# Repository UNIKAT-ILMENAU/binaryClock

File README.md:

# Notizen

## Idee

- QRCode mit Link auf Webseite für Flackercode Config Tool
- vllt Pads für I2C und ISP rausführen
- auf PCB, welche LED welcher Modus ist
- Comic Design? (muss zu Skyline passen)

## Hardware
- Fotodioden/transistoren
    - SFH 229 OSO
    - SFH 203
    - PT 334-6C EVL
    - SFH 309-5 OSO
    - SFH 300-3/4
- Batteriehalter: https://www.mouser.de/ProductDetail/Linx-Technologies/BAT-HLD-012-SMT?qs=Z0V%2FpEl%252BOGfZsSJil9WIXw%3D%3D
- Micro USB Port: https://www.mouser.de/ProductDetail/CUI-Devices/UJ2-MIBH-G-SMT-TR?qs=IS%252B4QmGtzzpvS1XQusp0iA%3D%3D

## Lötreihenfolge
- Quartz
- Widerstände
- LED
- Taster
- Sockel
- Kondensatoren

## Software
- https://forum.arduino.cc/t/time-libary-sommerzeit-winterzeit/221884

### Modi
Button 1: Select
Button 2: Plus
Button 3: Minus

Select rotiert durch die Zustände, Plus und Minus verändern den Wert

- TimeRunning, Zeit wird angezeigt und zählt          
- MenuYear, Jahr setzen
- MenuMonth, Monat setzen
- MenuDay, Tag setzen
- MenuHour, Stunden setzen
- MenuMinute, Minuten setzen
- MenuSecond, Sekunden setzen 

## ADC Calculation
| No. Switches    |           3 |        | Button No. | Req'd ADC | Req'd V (R1) | Req'd V (R2+) | Req'd R | Closest R | Actual V (R1) | Actual V (R2+) | Actual ADC | Diff from prev. | In Tolerance | Current (mA) |
|-----------------|------------:|--------|-----------:|----------:|-------------:|--------------:|--------:|----------:|--------------:|---------------:|-----------:|----------------:|-------------:|-------------:|
| ADC Resolution  |        1024 |        |          0 |      1024 |         0.00 |          5.00 |   47000 |     47000 |          5.00 |           0.00 |          0 |               0 |          N/A |         0.11 |
| Tolerance (%)   |           2 |        |          1 |       341 |         3.33 |          1.67 |   23500 |     24000 |          3.31 |           1.69 |        346 |             346 |          YES |         0.07 |
| Voltage         |           5 |        |          2 |       683 |         1.67 |          3.33 |   70500 |     68000 |          1.69 |           3.31 |        678 |             332 |          YES |         0.04 |
|                 |             |        |          3 |           |              |               |         |           |               |                |            |                 |              |              |
|                 |             |        |          4 |           |              |               |         |           |               |                |            |                 |              |              |
|                 |             |        |          5 |           |              |               |         |           |               |                |            |                 |              |              |
|                 |             |        |          6 |           |              |               |         |           |               |                |            |                 |              |              |
|                 |             |        |          7 |           |              |               |         |           |               |                |            |                 |              |              |
| ADC Tolerance   |       20.48 |  (+/-) |          8 |           |              |               |         |           |               |                |            |                 |              |              |
| Std. Deviation  | 10.27164132 |        |          9 |           |              |               |         |           |               |                |            |                 |              |              |
|                 |             |        |         10 |           |              |               |         |           |               |                |            |                 |              |              |
|                 |             |        |         11 |           |              |               |         |           |               |                |            |                 |              |              |

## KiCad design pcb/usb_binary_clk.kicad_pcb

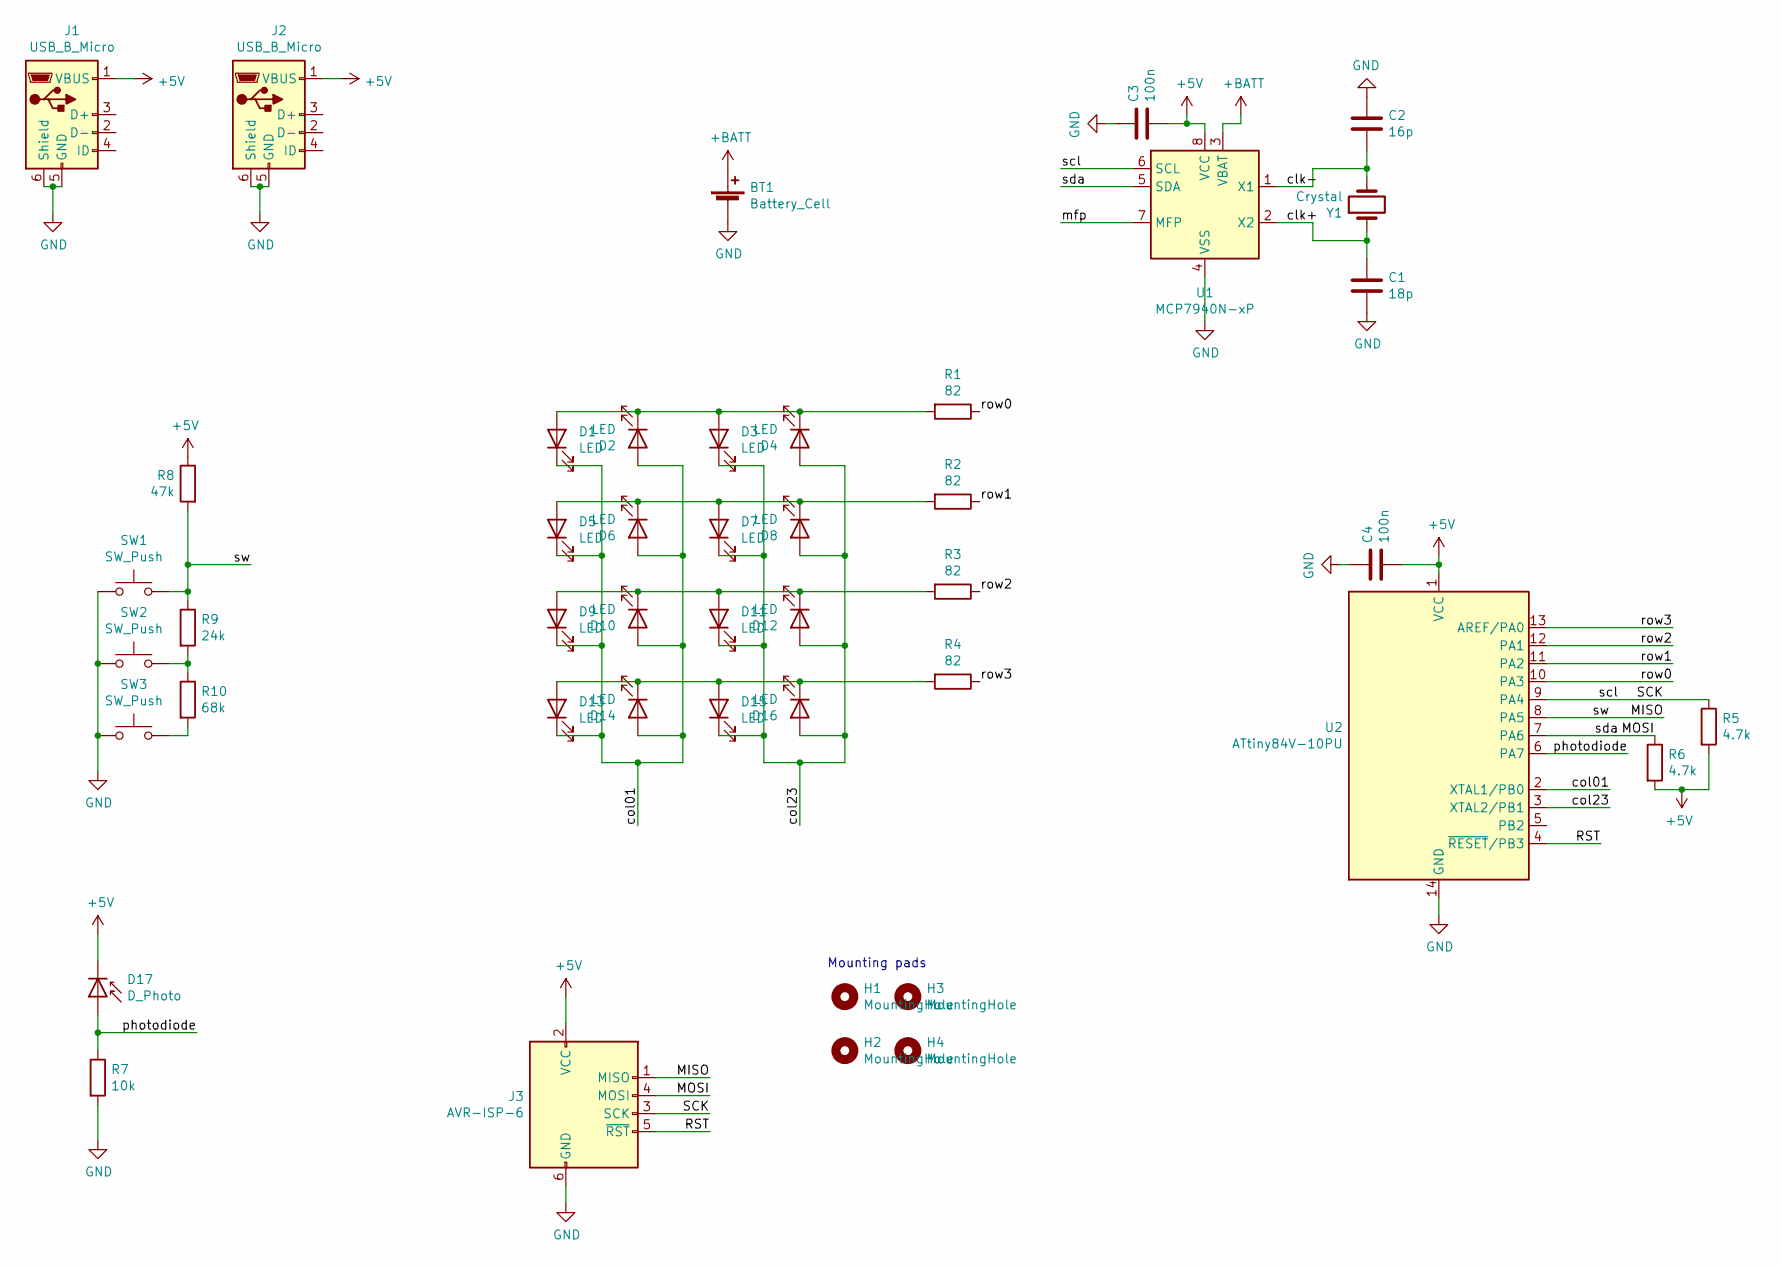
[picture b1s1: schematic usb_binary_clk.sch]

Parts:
BT1: Battery_Cell; bat-hld-012
C1: 18p; C_Disc_D4.3mm_W1.9mm_P5.00mm
C2: 16p; C_Disc_D4.3mm_W1.9mm_P5.00mm
C3, C4: 100n; C_Disc_D4.3mm_W1.9mm_P5.00mm
D1, D2, D3, D4, D5, D6, D7, D8, D9, D10, D11, D12, D13, D14, D15, D16: LED; LED_D5.0mm
D17: D_Photo; LED_D3.0mm
H1, H2, H3, H4: MountingHole; mountingPad_custom1
J1, J2: USB_B_Micro; UJ2MIBHGSMTTR
J3: AVR-ISP-6; isp_pogoPinPads
R1, R2, R3, R4: 82; R_Axial_DIN0207_L6.3mm_D2.5mm_P7.62mm_Horizontal
R5: 4.7k; R_Axial_DIN0207_L6.3mm_D2.5mm_P7.62mm_Horizontal
R6: 4.7k; R_Axial_DIN0207_L6.3mm_D2.5mm_P10.16mm_Horizontal
R7: 10k; R_Axial_DIN0207_L6.3mm_D2.5mm_P10.16mm_Horizontal
R8: 47k; R_Axial_DIN0207_L6.3mm_D2.5mm_P7.62mm_Horizontal
R9: 24k; R_Axial_DIN0207_L6.3mm_D2.5mm_P7.62mm_Horizontal
R10: 68k; R_Axial_DIN0207_L6.3mm_D2.5mm_P7.62mm_Horizontal
SW1, SW2, SW3: SW_Push; SW_PUSH_6mm_H4.3mm
U1: MCP7940N-xP; DIP-8_W7.62mm
U2: ATtiny84V-10PU; DIP-14_W7.62mm
Y1: Crystal; Crystal_AT310_D3.0mm_L10.0mm_Horizontal

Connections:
+5V: C3.2, C4.2, D17.1 (K), J1.1 (VBUS), J2.1 (VBUS), J3.2 (VCC), R5.2, R6.2, R8.1, U1.8 (VCC), U2.1 (VCC)
+BATT: BT1.1 (+), U1.3 (VBAT)
/MISO: J3.1 (MISO), R8.2, R9.1, SW1.1, U2.8 (PA5)
/MOSI: J3.4 (MOSI), R6.1, U1.5 (SDA), U2.7 (PA6)
/RST: J3.5 (~RST), U2.4 (~RESET~/PB3)
/SCK: J3.3 (SCK), R5.1, U1.6 (SCL), U2.9 (PA4)
/clk+: C1.1, U1.2 (X2), Y1.1
/clk-: C2.2, U1.1 (X1), Y1.2
/col01: D1.1 (K), D2.2 (A), D5.1 (K), D6.2 (A), D9.1 (K), D10.2 (A), D13.1 (K), D14.2 (A), U2.2 (XTAL1/PB0)
/col23: D3.1 (K), D4.2 (A), D7.1 (K), D8.2 (A), D11.1 (K), D12.2 (A), D15.1 (K), D16.2 (A), U2.3 (XTAL2/PB1)
/mfp: U1.7 (MFP)
/photodiode: D17.2 (A), R7.1, U2.6 (PA7)
/row0: R1.1, U2.10 (PA3)
/row1: R2.1, U2.11 (PA2)
/row2: R3.1, U2.12 (PA1)
/row3: R4.1, U2.13 (AREF/PA0)
GND: BT1.2 (-), C1.2, C2.1, C3.1, C4.1, J1.5 (GND), J1.6 (Shield), J2.5 (GND), J2.6 (Shield), J3.6 (GND), R7.2, SW1.2, SW2.2, SW3.2, U1.4 (VSS), U2.14 (GND)
unnamed: D1.2 (A), D2.1 (K), D3.2 (A), D4.1 (K), R1.2
unnamed: D5.2 (A), D6.1 (K), D7.2 (A), D8.1 (K), R2.2
unnamed: D9.2 (A), D10.1 (K), D11.2 (A), D12.1 (K), R3.2
unnamed: D13.2 (A), D14.1 (K), D15.2 (A), D16.1 (K), R4.2
unnamed: R9.2, R10.1, SW2.1
unnamed: R10.2, SW3.1

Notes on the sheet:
Mounting pads

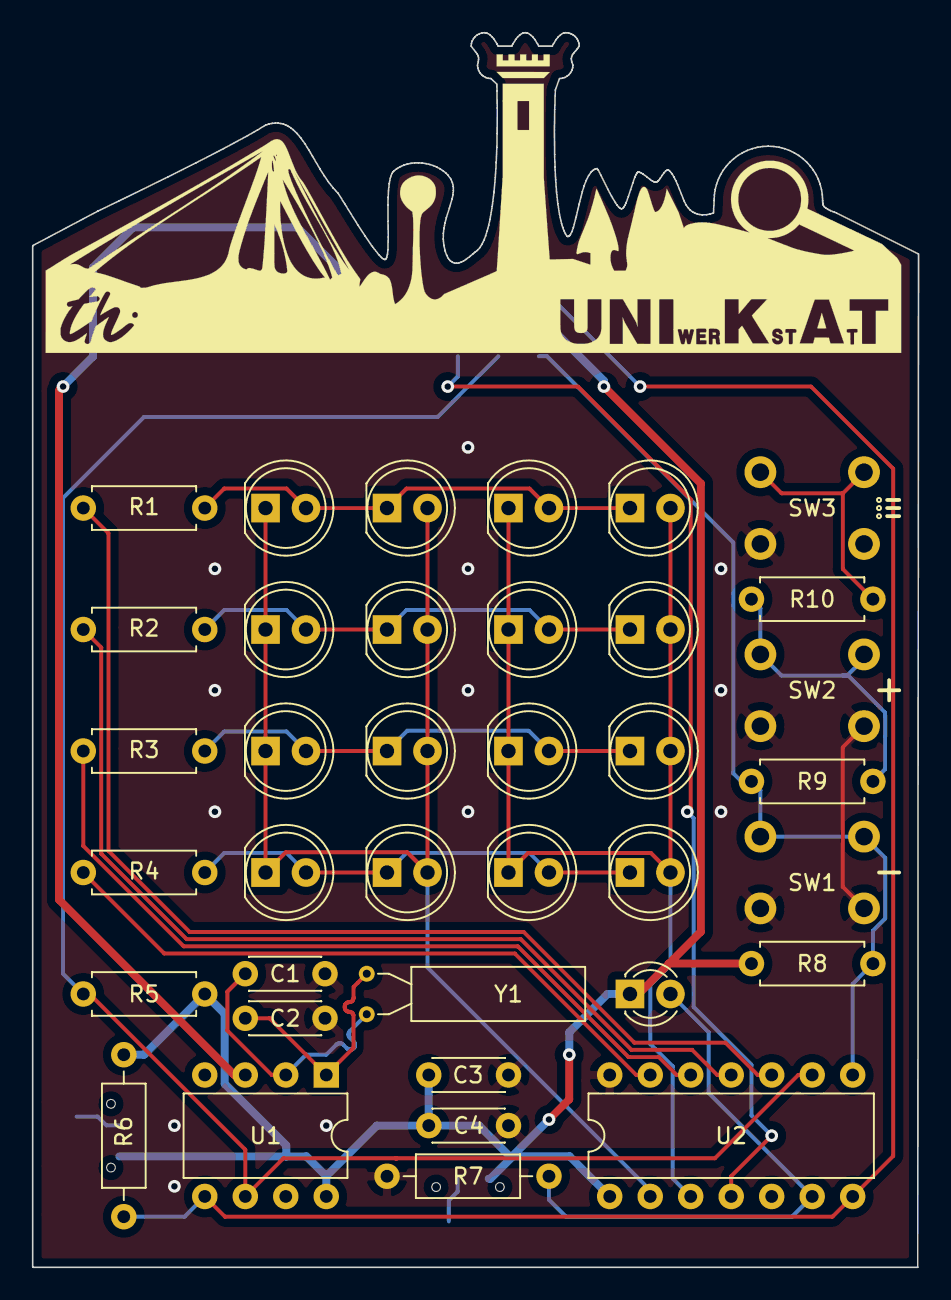
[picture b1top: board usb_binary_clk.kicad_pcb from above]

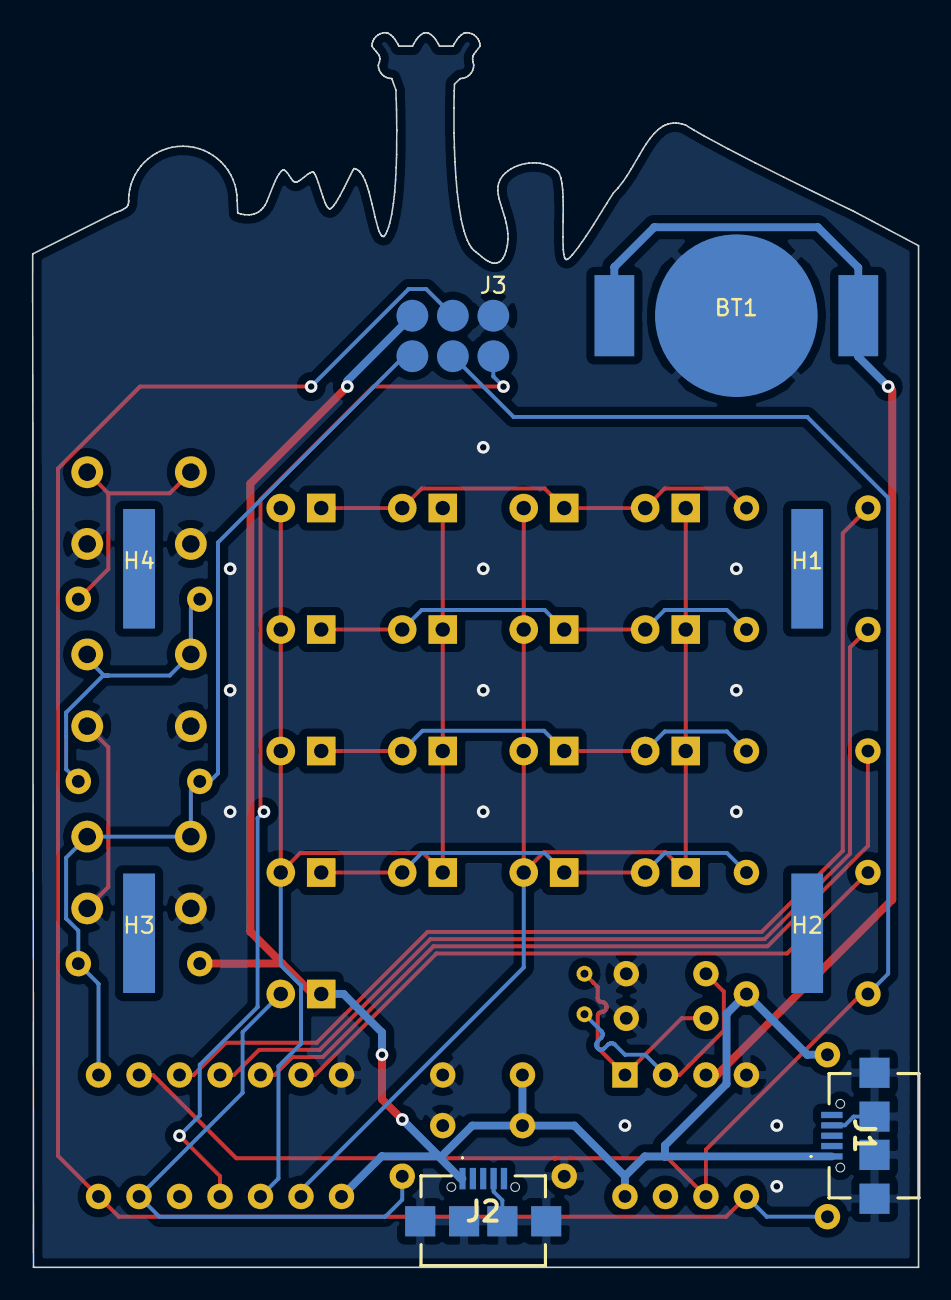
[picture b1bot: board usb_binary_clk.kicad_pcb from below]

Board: 2 copper layers, 55.6 x 77.4 mm, 45 parts (8 on the bottom side), 22 nets.

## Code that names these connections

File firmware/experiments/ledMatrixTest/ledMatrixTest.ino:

#define ROW0 0
#define ROW1 1
#define ROW2 2
#define ROW3 3
#define COL0 7
#define COL1 10
#define COL2 9
#define COL3 8

const int COL[] = {COL0, COL1, COL2, COL3};
const int ROW[] = {ROW0, ROW1, ROW2, ROW3};

void setup() {
  pinMode(ROW0, OUTPUT);
  pinMode(ROW1, OUTPUT);
  pinMode(ROW2, OUTPUT);
  pinMode(ROW3, OUTPUT);
  pinMode(COL0, OUTPUT);
  pinMode(COL1, OUTPUT);
  pinMode(COL2, OUTPUT);
  pinMode(COL3, OUTPUT);
}



void setCol(uint8_t col, uint8_t y) {
  digitalWrite(COL0, HIGH);
  digitalWrite(COL1, HIGH);
  digitalWrite(COL2, HIGH);
  digitalWrite(COL3, HIGH);

  digitalWrite(COL[col], LOW);
  
  digitalWrite(ROW0, y&0b0001);
  digitalWrite(ROW1, y&0b0010);
  digitalWrite(ROW2, y&0b0100);
  digitalWrite(ROW3, y&0b1000);
  
}

void loop() {
  setCol(0, 0b1010); 
  setCol(1, 0b1010);
  setCol(2, 0b1010); 
  setCol(3, 0b1010);
  //setCol(0, 0b0000);
  //delay(10);
}

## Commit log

2021-08-19 renamed pcb folder
2021-08-19 fixed .gitignore
2021-08-19 added README
2021-08-19 added part values, shold be done
2021-08-19 resistor ladder fixed
2021-08-26 added schematic pdf
2021-08-26 Add led matrix test arduino code
2021-09-02 pio firmware test
2021-09-02 Convert code to platformio
2021-09-02 Add basic MCP7940 readout
2021-09-09 Fancy Matrix Code
2021-09-16 Set and read time
2021-10-16 Read buttons when changed or hold with debounce and update leds faster
2021-10-17 Correct row order
2021-10-24 matrix test code
2021-10-28 Remove glow in leds by optimising port writes
2021-10-28 Improved led matrix to use up less pins
2021-10-31 Add brightness control
2021-10-31 Make pwm better
2021-10-31 added phototransistor
2021-11-07 Display, Frequency, schematic fix, ideas, led components
2021-11-18 linked symbols to footprints, started arranging/modding them
2021-11-18 Modify pcb layout
2021-11-25 add pcb skyline + logos
2021-12-02 fix pcb design
2021-12-02 fix pcb design (for real this time)
2021-12-02 finalizes part position
2021-12-09 fix broken schematic symbols
2021-12-09 change usb port footprints, add programmer pads
2021-12-16 add routing
2021-12-16 add routing (forgot to save last time)
2022-01-06 tune crystal paths, add vias
2022-01-13 rearrange footprint references + add icons
2022-01-13 connect programmer; add qr code; create gerber files for first order
2022-01-13 safety commit
2022-02-10 Add brightness control, remove OLED code, swap menu buttons
2022-03-17 update schematic pdf
2022-03-24 move via out of printed part
    fix #4
2022-03-24 add mounting pads for stand/wall mount
    fix #7
2022-04-04 add ordering excel sheet
2022-04-18 update bestellliste and add pdf version
2022-04-18 attempt to compensate for printing errors in silk screen
2022-04-18 update gerber files
2022-04-18 update gerber files (again)
2022-04-19 Revert "update gerber files (again)"
    This reverts commit 1e2eee7170581ef00778106c54266a2a04ba0844.
2022-04-19 fix silkscreen printing issues
    close #5
2022-04-19 change photodiode footprint to 3mm
2022-04-19 update gerbers for ordering
2022-04-19 remove back silkscreen file from gerbers
2022-06-16 fix fuses
2022-07-14 display hours and minutes; add blinking led in menu
2022-07-24 Add handout
2022-08-03 Fix LED description
2022-08-03 Fix ghost button presses
2022-08-04 Update PDF
2022-08-05 fix false button presses
2022-08-05 add notes in schematic
2022-08-29 rename firmware folder
2023-11-12 Enable battery backup on MCP
